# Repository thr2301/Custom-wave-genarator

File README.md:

# Costum Signal Generator ⚡

An open-source, fully analog function generator built around the **TL074 quad operational amplifier**. This project generates simultaneous Triangle, Square, and Sine waves. It features a discrete, mathematical piecewise-linear diode wave shaper, adjustable output buffering, and a low-noise split-rail power design.

Designed and routed in **KiCad 8**, with complete circuit simulation available for **LTspice**.

---

## 📑 Table of Contents
1. [Key Features](#-key-features)
2. [Theory of Operation](#-theory-of-operation)
3. [LTspice Simulation](#-ltspice-simulation)
4. [Component Selection Guide](#-component-selection-guide)
5. [PCB Design & Layout](#-pcb-design--layout)
6. [Calibration & Tuning](#-calibration--tuning)

---

## ✨ Key Features
* **Tri-Wave Output:** Generates Square, Triangle, and Sine waves from a single TL074 IC.
* **Low-THD Sine Wave:** Utilizes a custom multi-stage diode clipping network with precise bias voltages to perfectly round off the triangle wave.
* **Master Volume Control:** Integrated Bourns 3296P multi-turn trimmer for fine amplitude adjustment (0% to 100%) without degrading waveform symmetry.
* **Output Isolation:** The 4th op-amp acts as a unity-gain output buffer, protecting the delicate internal wave shaper from external loads and impedance mismatches.
* **High-Fidelity Audio Range:** Tuned for the ~1kHz audio spectrum (easily modifiable for LFO or higher-frequency RF applications).
* **Split-Rail Power:** Optimized for standard ±15V dual power supplies for maximum headroom and signal clarity.

---

## 🧠 Theory of Operation

### 1. The Core Oscillator (Square & Triangle)
The foundation of the generator uses **U1** and **U2** in a classic relaxation oscillator topology:
* **U1 (Schmitt Trigger):** Acts as a comparator with hysteresis. It outputs a square wave that slams between the +15V and -15V rails.
* **U2 (Integrator):** Takes the harsh square wave and mathematically integrates it using a feedback capacitor (`C1`). A constant positive voltage turns into a downward-sloping ramp, and a constant negative voltage turns into an upward-sloping ramp—yielding a perfect Triangle wave.
* The Triangle wave is fed back into the Schmitt Trigger. The threshold at which the trigger reverses direction is set by the ratio of the feedback resistors (`R1` and `R2`), which directly determines the Triangle wave's peak-to-peak amplitude.

### 2. The Diode Wave Shaper (Sine)
Because building a pure analog sine wave oscillator is inherently unstable, this circuit uses a **Piecewise Linear Approximation Shaper** around **U3**:
* The raw Triangle wave is passed through a voltage divider network containing parallel branches of **1N4148 small-signal diodes**.
* Each branch is tied to a specific DC bias voltage (e.g., ±1.5V and ±3.0V). 
* As the Triangle wave's voltage rises, it sequentially turns on these diodes. Each activated branch drops the equivalent resistance of the network, gently reducing the gain and "bending" the straight slope of the triangle wave to approximate the curve of a pure sine wave.

### 3. The Output Stage
* **U4 (Unity Gain Buffer):** To ensure the sine wave doesn't collapse when plugged into an oscilloscope or audio interface, a 100kΩ volume potentiometer divides the final signal and feeds it into the Non-Inverting (`+`) input of U4. The output is a robust, low-impedance signal capable of driving external gear.

---

## 💻 LTspice Simulation

Before modifying the PCB, you can test resistor changes in the provided LTspice `.asc` file. 

**Pro-Tips for Simulation:**
* ** Voltage divivers are used instead of trimmmers in some cases
* ** Transient analysis is used

---

## 🔬 Component Selection Guide

To achieve a clean, low-distortion waveform, component quality is critical:
* **Resistors:** Use **1% tolerance metal film** resistors. The wave shaper relies on precise math; carbon resistors with 5% variance will result in a lopsided sine wave.
* **Capacitors (Timing):** `C1` must be a **Film Capacitor** (Polyester/Mylar or Polypropylene). Ceramic capacitors suffer from microphonics and temperature drift, which will cause your frequency to wander.
* **Capacitors (Bypass):** The 0.1µF decoupling caps placed near the TL074 power pins should be standard **MLCC ceramics** for the fastest high-frequency noise rejection.
* **Diodes:** You *must* use **1N4148** or **1N914** small-signal fast-switching diodes. Do not substitute with power rectifiers like the 1N4007 or 1N4937, as their forward voltage curves and junction capacitance will ruin the high-frequency response.

---

## 📐 PCB Design & Layout

If modifying the KiCad `.kicad_pcb` layout, adhere to these analog routing guidelines:
1. **Copper Pours:** The board features grounded copper fills on both the `F.Cu` and `B.Cu` layers to shield the sensitive wave shaper from EMI.
   
3. **Decoupling Placement:** The bypass capacitors are physically routed millimetres away from Pin 4 (+15V) and Pin 11 (-15V) of the TL074 to absorb transient switching spikes from the square wave generator.
   
5. **Trace Widths:** Analog signal traces are routed at `0.25mm` (10 mil), while the power rails (`+15V`, `-15V`) are thickened to `0.5mm` (20 mil) to minimize voltage drop.

---

## ⚙️ Calibration & Tuning

Once assembled, you will need an oscilloscope to calibrate the device:
1. **Power Up:** Connect a ±15V lab supply to the power terminal.
2. **Check the Triangle:** Probe the output of U2. You should see a sharp, symmetrical triangle wave. 
3. **Tune the Volume:** Probe the final output of U4. Slowly turn the `RV1` Bourns trimmer clockwise with a flathead screwdriver. The sine wave should grow in amplitude without flat-lining (clipping) at the top or bottom.
4. **THD Minimization (Advanced):** If the sine wave has sharp "points" at the peaks, the input triangle wave is too large. You can drop the value of `R2` slightly to lower the Schmitt trigger threshold until the wave rounds out perfectly.

---

## TODO
Upload the pcb with soldered components when is ready

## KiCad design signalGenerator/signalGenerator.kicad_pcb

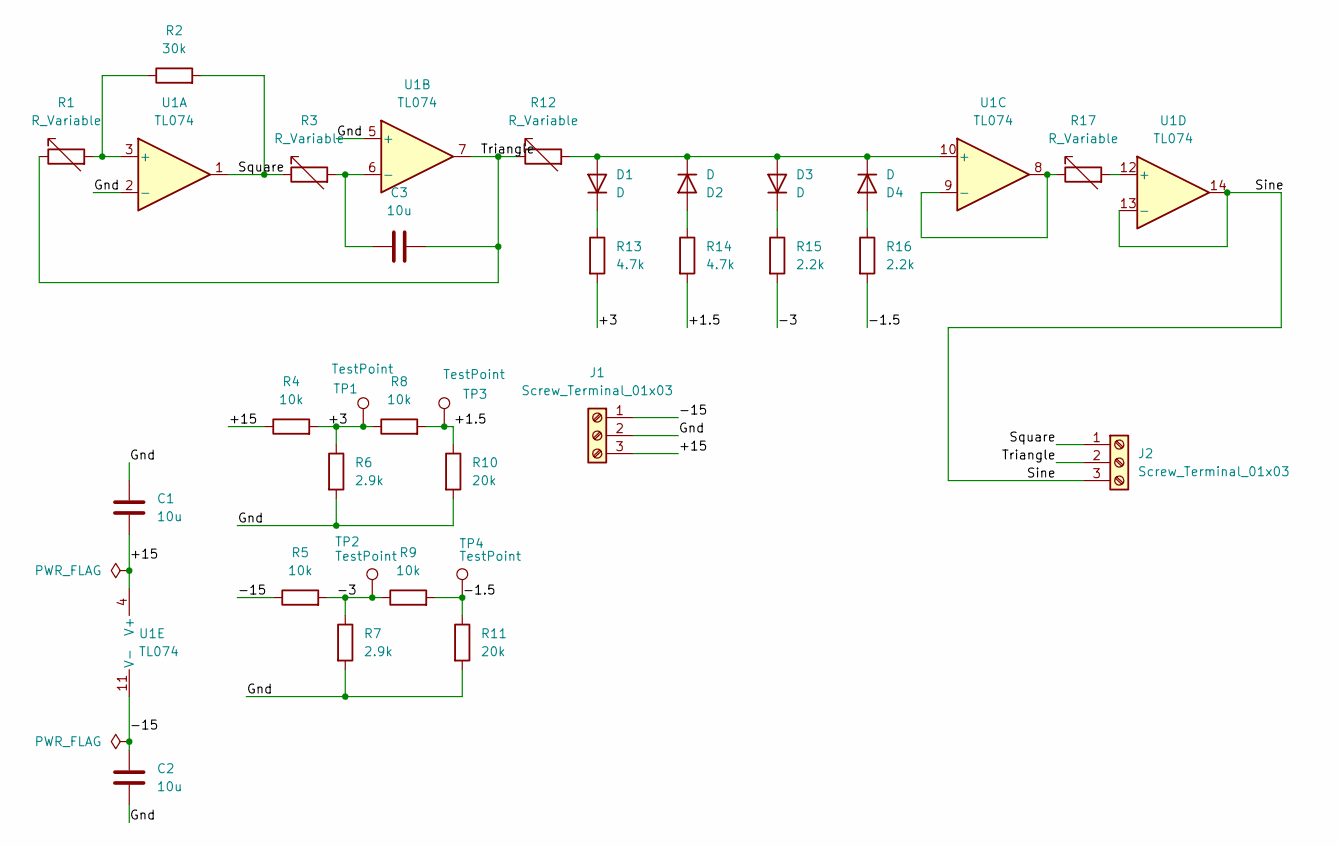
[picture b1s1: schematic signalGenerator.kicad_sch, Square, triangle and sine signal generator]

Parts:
C1, C2, C3: 10u; C_Disc_D5.0mm_W2.5mm_P5.00mm
D1, D2, D3, D4: D; D_DO-35_SOD27_P7.62mm_Horizontal
J1, J2: Screw_Terminal_01x03; TerminalBlock_Phoenix_MKDS-1,5-3_1x03_P5.00mm_Horizontal
R1, R3, R12, R17: R_Variable; Potentiometer_Bourns_3296P_Horizontal
R2: 30k; R_Axial_DIN0207_L6.3mm_D2.5mm_P7.62mm_Horizontal
R4, R5, R8, R9: 10k; R_Axial_DIN0207_L6.3mm_D2.5mm_P7.62mm_Horizontal
R6, R7: 2.9k; R_Axial_DIN0207_L6.3mm_D2.5mm_P7.62mm_Horizontal
R10, R11: 20k; R_Axial_DIN0207_L6.3mm_D2.5mm_P7.62mm_Horizontal
R13, R14: 4.7k; R_Axial_DIN0207_L6.3mm_D2.5mm_P7.62mm_Horizontal
R15, R16: 2.2k; R_Axial_DIN0207_L6.3mm_D2.5mm_P7.62mm_Horizontal
TP1, TP2, TP3, TP4: TestPoint; TestPoint_Keystone_5000-5004_Miniature
U1: TL074; DIP-14_W7.62mm

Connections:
/+1.5: R8.2, R10.1, R14.2, TP3.1 (1_1)
/+3: R4.2, R6.1, R8.1, R13.2, TP1.1 (1_1)
/+15: C1.1, J1.3, R4.1, U1.4 (V+)
/-1.5: R9.2, R11.1, R16.2, TP4.1 (1_1)
/-3: R5.2, R7.1, R9.1, R15.2, TP2.1 (1_1)
/-15: C2.1, J1.1, R5.1, U1.11 (V-)
/Gnd: C1.2, C2.2, J1.2, R6.2, R7.2, R10.2, R11.2, U1.2 (-), U1.5 (+)
/Sine: J2.3, U1.13 (-), U1.14
/Square: J2.1, R2.2, R3.1, U1.1
/Triangle: C3.2, J2.2, R1.1, R12.1, U1.7
unnamed: D1.2 (A), D2.1 (K), D3.2 (A), D4.1 (K), R12.2, U1.10 (+)
unnamed: D1.1 (K), R13.1
unnamed: D2.2 (A), R14.1
unnamed: D3.1 (K), R15.1
unnamed: D4.2 (A), R16.1
unnamed: R1.2, R2.1, U1.3 (+)
unnamed: C3.1, R3.2, U1.6 (-)
unnamed: R17.1, U1.8, U1.9 (-)
unnamed: R17.2, U1.12 (+)

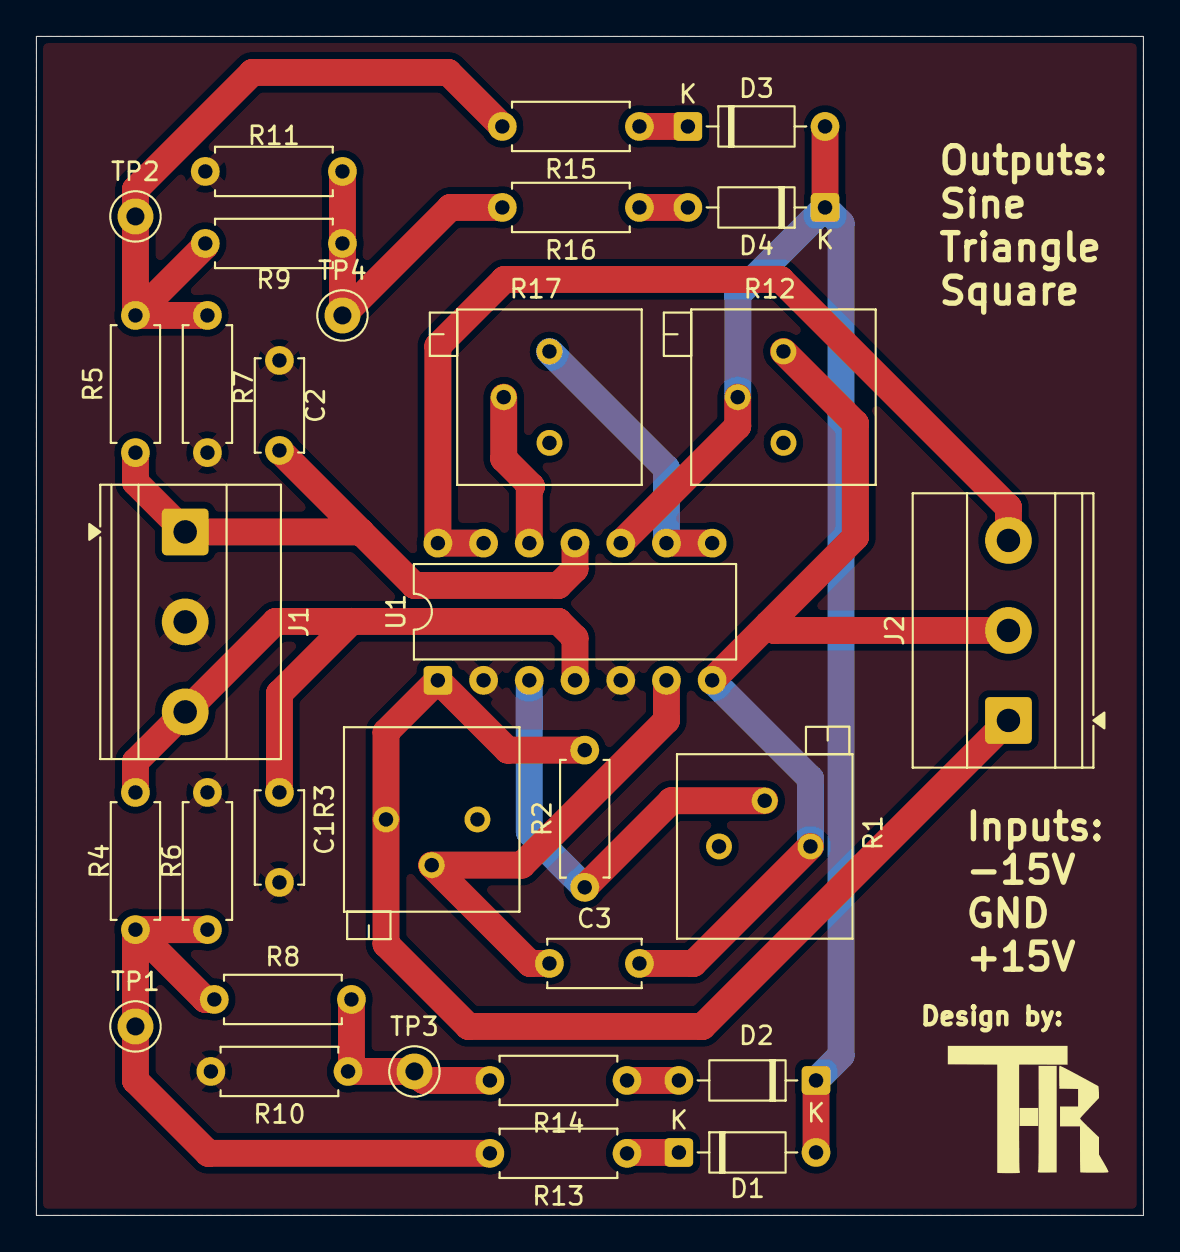
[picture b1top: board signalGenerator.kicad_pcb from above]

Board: 2 copper layers, 61.5 x 65.5 mm, 31 parts (0 on the bottom side), 19 nets.
